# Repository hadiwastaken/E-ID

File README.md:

# E-ID

**WHAT IS IT**
*SO BASICALLY THIS IS A BADGE OR ID IN A DIGITAL CARD BASICALLY I BUILD THIS MAINLY O UNDERSTAND PCB WORKING AND FOR FIRMWARE I REALLY AMDE IT SIMPLE BECUZ I WANT TO UNDERSTAND FIRMWARE I AM NOT FIMILAR WITH CODE .

**FEATURES**
* IT INCLUDE A ESP-32 WROOM 32D DEVELOPMENT BOARD WHICH HAS A BUILT IN WIFI AND USB C CABLE.
* I USE A ST7789 TFT DISPLAY WHICH IS A GOOOD AND CHEAP OPTION
* I ALSO MADE A PCB FOR PERMANENT WIRING.
* ITS ESPECIALTY IS THAT IT DISPLAYS YOUR ID CARD ON A CUTE DISPLAY
* 2 CAPACITORS TO CONTROL FLICKERING ONES VALUE IS 10UF AND THE OTHER ONE IS 0.1UF.
* ALSO SOME COOL STICKER ON PCB .
**IMAGES**
*PCB EDITOR VIEW:

*SCHEMATICS:

*DRC ERRORS:

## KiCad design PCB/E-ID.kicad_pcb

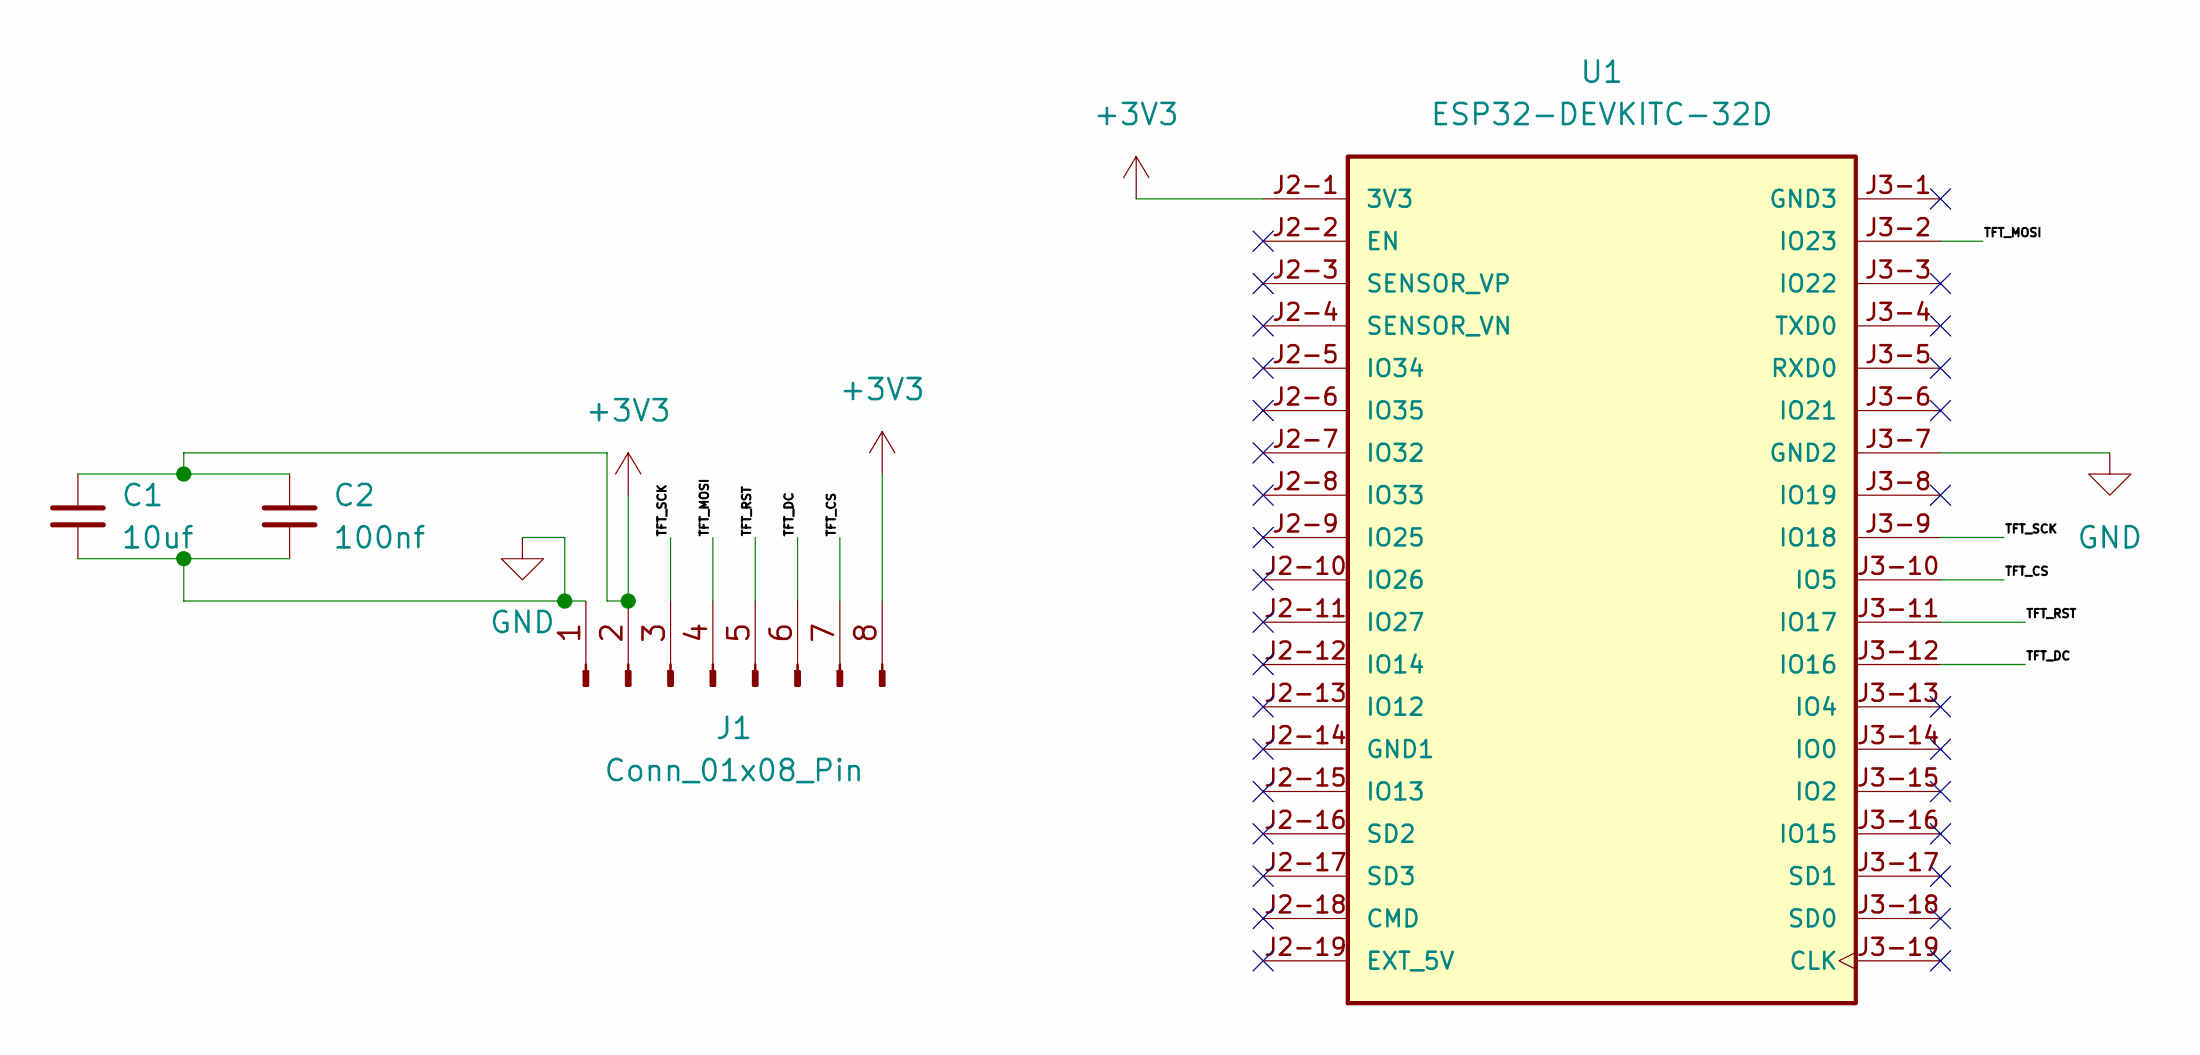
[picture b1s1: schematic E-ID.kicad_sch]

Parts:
C1: 10uf; C_0805_2012Metric_Pad1.18x1.45mm_HandSolder
C2: 100nf; C_0805_2012Metric_Pad1.18x1.45mm_HandSolder
J1: Conn_01x08_Pin; PinSocket_1x08_P2.54mm_Vertical
U1: ESP32-DEVKITC-32D; MODULE_ESP32-DEVKITC-32D; PARTREV V4

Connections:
+3V3: C1.1, C2.1, J1.2, J1.8, U1.J2-1 (3V3)
/TFT_CS: J1.7, U1.J3-10 (IO5)
/TFT_DC: J1.6, U1.J3-12 (IO16)
/TFT_MOSI: J1.4, U1.J3-2 (IO23)
/TFT_RST: J1.5, U1.J3-11 (IO17)
/TFT_SCK: J1.3, U1.J3-9 (IO18)
GND: C1.2, C2.2, J1.1, U1.J3-7 (GND2)

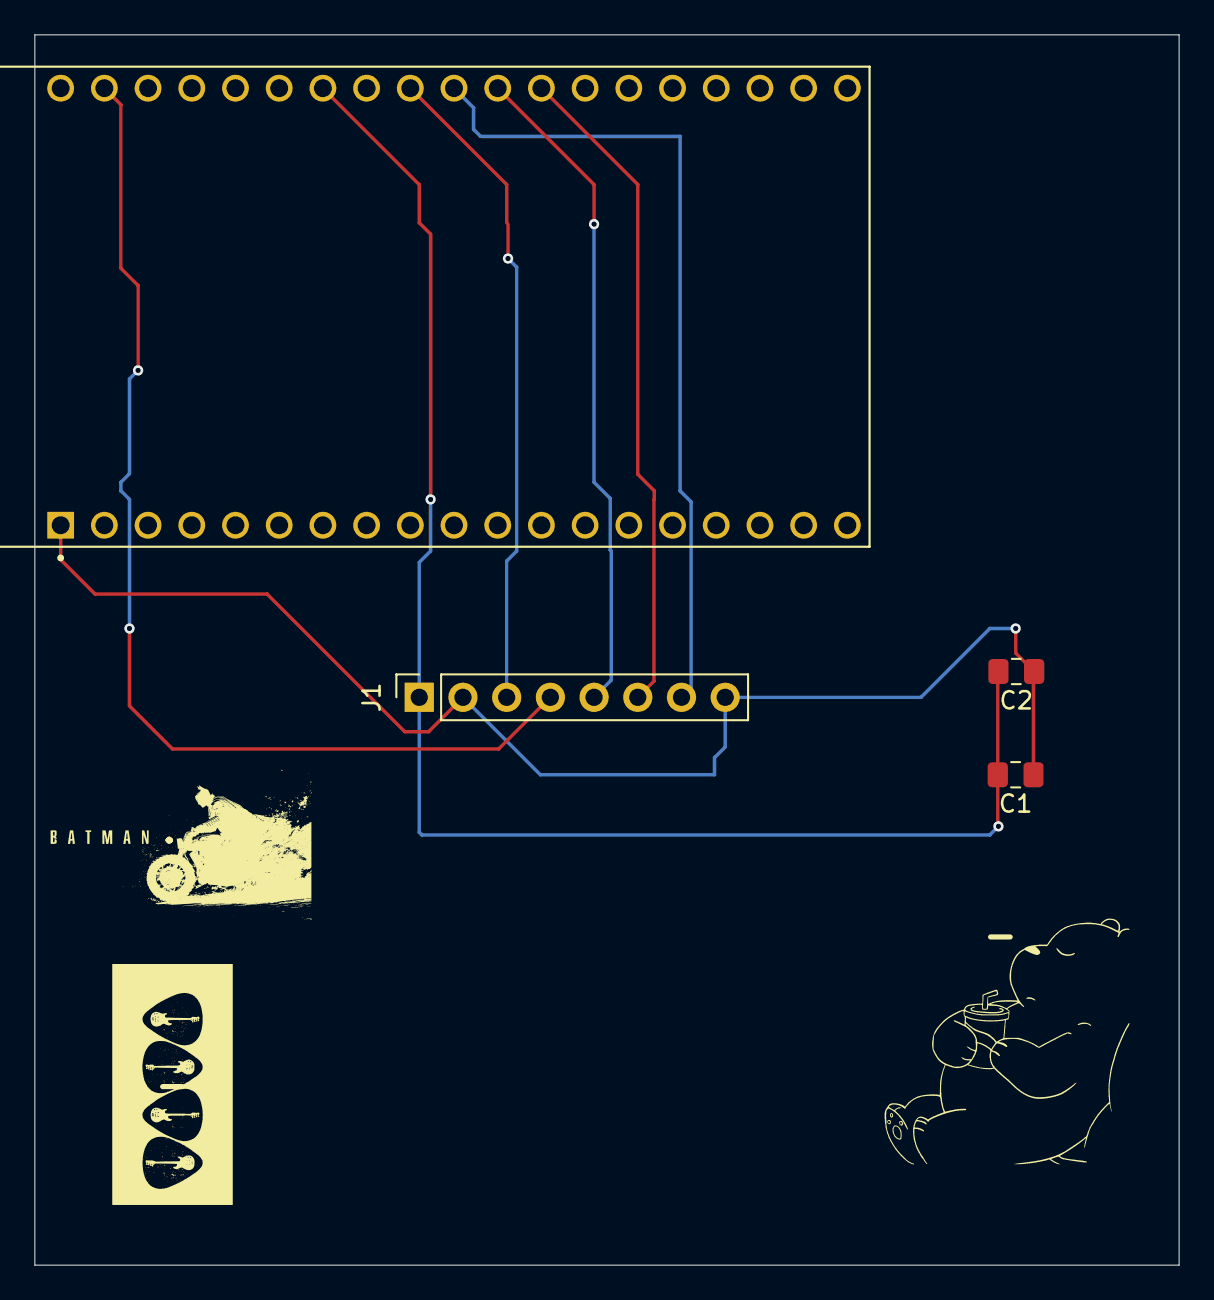
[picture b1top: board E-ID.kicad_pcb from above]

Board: 2 copper layers, 66.5 x 71.5 mm, 7 parts (0 on the bottom side), 7 nets.

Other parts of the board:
-: LOGO
-#2: LOGO
.: LOGO

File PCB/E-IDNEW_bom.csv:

Designator,Footprint,Quantity,Value,LCSC Part #
C1,0805,1,10uf,
C2,0805,1,100nf,
J1,PinSocket_1x08_P2.54mm_Vertical,1,Conn_01x08_Pin,
U1,MODULE_ESP32-DEVKITC-32D,1,ESP32-DEVKITC-32D,

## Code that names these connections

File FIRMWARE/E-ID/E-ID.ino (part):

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#include <Adafruit_ST7789.h>
#include <SPI.h>
//------------------------------------------------------------------------------
#define TFT_CS     5
#define TFT_DC     16
#define TFT_RST    17

Adafruit_ST7789 tft = Adafruit_ST7789(TFT_CS,TFT_DC,TFT_RST);

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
